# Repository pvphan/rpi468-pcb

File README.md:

'Raspberry Pi 468' PCB files
---

This repo contains the PCB model files for the RPi 468
For more details, see my blog post here: [pvphan.com](https://pvphan.com)

Links to these PCB projects on OSHPark:
- [USB host switching circuit](https://oshpark.com/shared_projects/PfGfJg1X)
- [Mini USB pad to JST](https://oshpark.com/shared_projects/LUSGZfi8)

The USB host switching circuit solder in place of the Raspberry Pi 400 USB-A 2.0 port

The USB host switching circuit, mostly soldered

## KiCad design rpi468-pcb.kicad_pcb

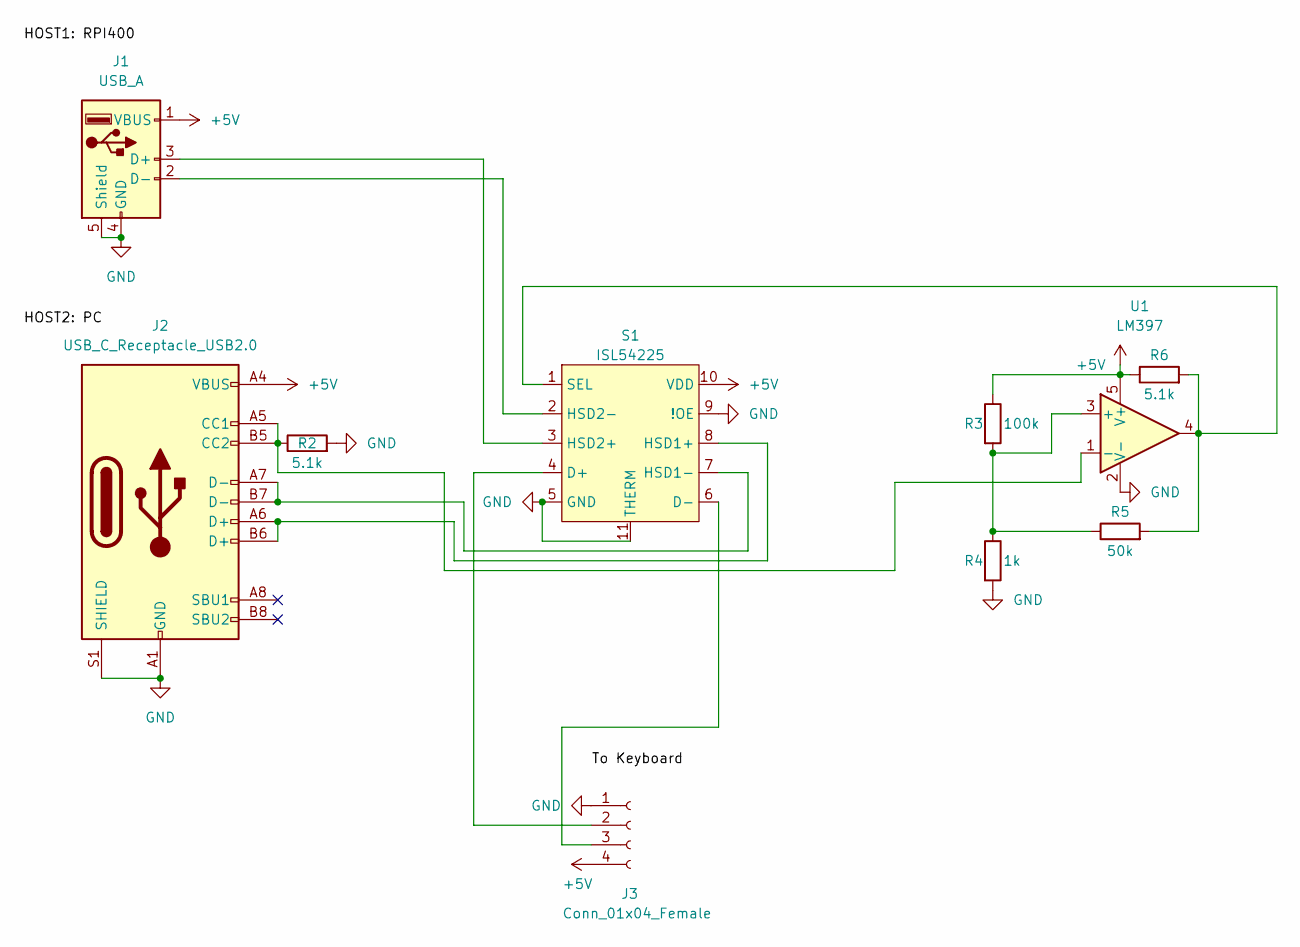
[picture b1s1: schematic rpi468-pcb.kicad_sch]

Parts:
J1: USB_A; USB_A_Molex_67643_Horizontal
J2: USB_C_Receptacle_USB2.0; USB_C_Receptacle_Amphenol_12401610E4-2A
J3: Conn_01x04_Female; JST_SH_BM04B-SRSS-TB_1x04-1MP_P1.00mm_Vertical
R2, R6: 5.1k; R_0603_1608Metric_Pad0.98x0.95mm_HandSolder
R3: 100k; R_0603_1608Metric_Pad0.98x0.95mm_HandSolder
R4: 1k; R_0603_1608Metric_Pad0.98x0.95mm_HandSolder
R5: 50k; R_0603_1608Metric_Pad0.98x0.95mm_HandSolder
S1: ISL54225; DFN-10-1EP_3x3mm_P0.5mm_EP1.75x2.7mm
U1: LM397; SOT-23-5

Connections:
+5V: J1.1 (VBUS), J2.A4 (VBUS), J2.A9 (VBUS), J2.B4 (VBUS), J2.B9 (VBUS), J3.4, R3.1, R6.1, S1.10 (VDD), U1.5 (V+)
GND: J1.4 (GND), J1.5 (Shield), J2.A1 (GND), J2.A12 (GND), J2.B1 (GND), J2.B12 (GND), J2.S1 (SHIELD), J3.1, R2.2, R4.2, S1.5 (GND), S1.9 (!OE), S1.11 (THERM), U1.2 (V-)
unnamed: J1.2 (D-), S1.2 (HSD2-)
unnamed: J1.3 (D+), S1.3 (HSD2+)
unnamed: J2.A5 (CC1), J2.B5 (CC2), R2.1, U1.1 (-)
unnamed: J2.A6 (D+), J2.B6 (D+), S1.8 (HSD1+)
unnamed: J2.A7 (D-), J2.B7 (D-), S1.7 (HSD1-)
unnamed: R3.2, R4.1, R5.1, U1.3 (+)
unnamed: R5.2, R6.2, S1.1 (SEL), U1.4
unnamed: J3.2, S1.4 (D+)
unnamed: J3.3, S1.6 (D-)

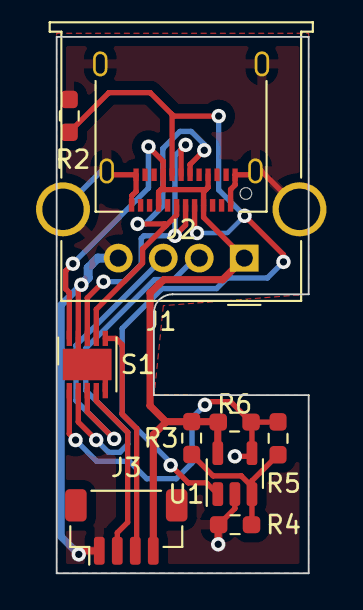
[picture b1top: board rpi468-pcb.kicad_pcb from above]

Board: 2 copper layers, 14.0 x 29.8 mm, 10 parts (0 on the bottom side), 11 nets.

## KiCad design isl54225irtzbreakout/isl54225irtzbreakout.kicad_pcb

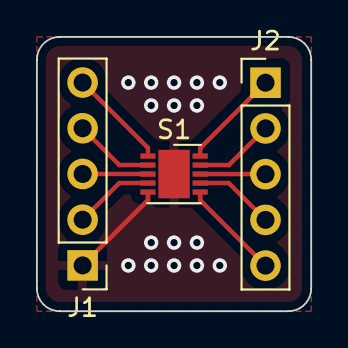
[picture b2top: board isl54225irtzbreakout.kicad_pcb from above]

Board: 2 copper layers, 15.2 x 15.2 mm, 3 parts (0 on the bottom side), 10 nets.

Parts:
J1, J2: Conn_01x05; PinHeader_1x05_P2.54mm_Vertical
S1: ISL54225; DFN-10-1EP_3x3mm_P0.5mm_EP1.75x2.7mm

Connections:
GND: J1.1, S1.5 (GND), S1.11 (THERM)
unnamed: J1.2, S1.4 (D+)
unnamed: J1.3, S1.3 (HSD2+)
unnamed: J1.4, S1.2 (HSD1+)
unnamed: J1.5, S1.1 (SEL)
unnamed: J2.1, S1.10 (VDD)
unnamed: J2.2, S1.9 (!OE)
unnamed: J2.3, S1.8 (HSD1-)
unnamed: J2.4, S1.7 (HSD2-)
unnamed: J2.5, S1.6 (D-)

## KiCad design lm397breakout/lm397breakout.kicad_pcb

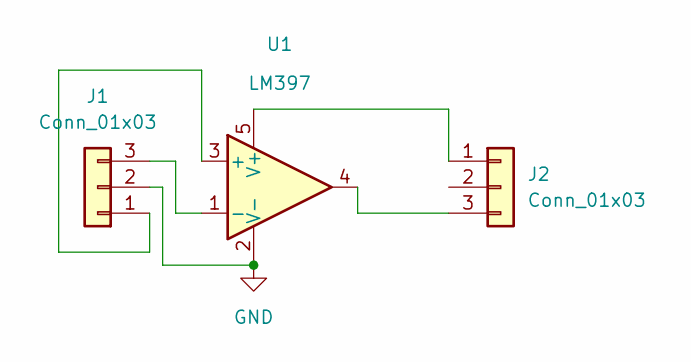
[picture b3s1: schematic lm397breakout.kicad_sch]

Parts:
J1: Conn_01x03
J2: Conn_01x03; PinHeader_1x03_P2.54mm_Vertical
U1: LM397; SOT-23-5

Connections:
GND: J1.2, U1.2 (V-)
unnamed: J1.1, U1.3 (+)
unnamed: J1.3, U1.1 (-)
unnamed: J2.1, U1.5 (V+)
unnamed: J2.3, U1.4

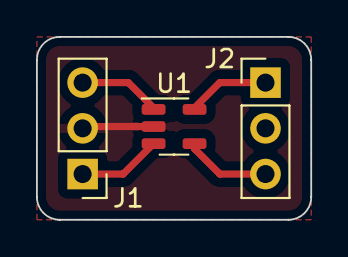
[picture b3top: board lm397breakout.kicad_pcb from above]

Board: 2 copper layers, 15.2 x 10.2 mm, 3 parts (0 on the bottom side), 5 nets.

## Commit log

2022-06-07 added ignore
2022-06-07 commiting files
2022-06-20 added breakout boardk
2022-06-20 rounded edges of breakout
2022-06-20 added new breakout for ISL54225
2022-06-22 close to target values
2022-06-22 reasonable resistor values
2022-06-23 started layout
2022-06-23 moved some components
2022-06-24 trying to route
2022-07-06 fixed bug, schematic works for breadboard
2022-07-06 layingout the board again
2022-07-06 updated layout a little
2022-07-06 made some tracks
2022-07-08 routing seems more reasonable, still need to refer to mCAD for actual cut profile
2022-07-08 cleaned up some traces
2022-07-21 added outline
2022-07-22 routing close to done
2022-07-22 finished routing
2022-07-22 updated board for 1mm pitch connector, reran some traces
2022-07-22 some cleanup
2022-07-27 added usb-c to model
2022-08-07 bridging CC1 and CC2
2022-08-10 updated pcb
2022-08-10 ignoring cad files
2022-08-10 updated cut outline
2022-08-11 added to ignore file
2022-08-11 added note
2022-08-13 added connector board
2023-05-20 added images and readme
2023-05-20 downscaling images
2023-05-20 removed downscale tags
2023-05-20 fixing blog link
2023-05-20 added https
2023-05-20 added oshpark links
